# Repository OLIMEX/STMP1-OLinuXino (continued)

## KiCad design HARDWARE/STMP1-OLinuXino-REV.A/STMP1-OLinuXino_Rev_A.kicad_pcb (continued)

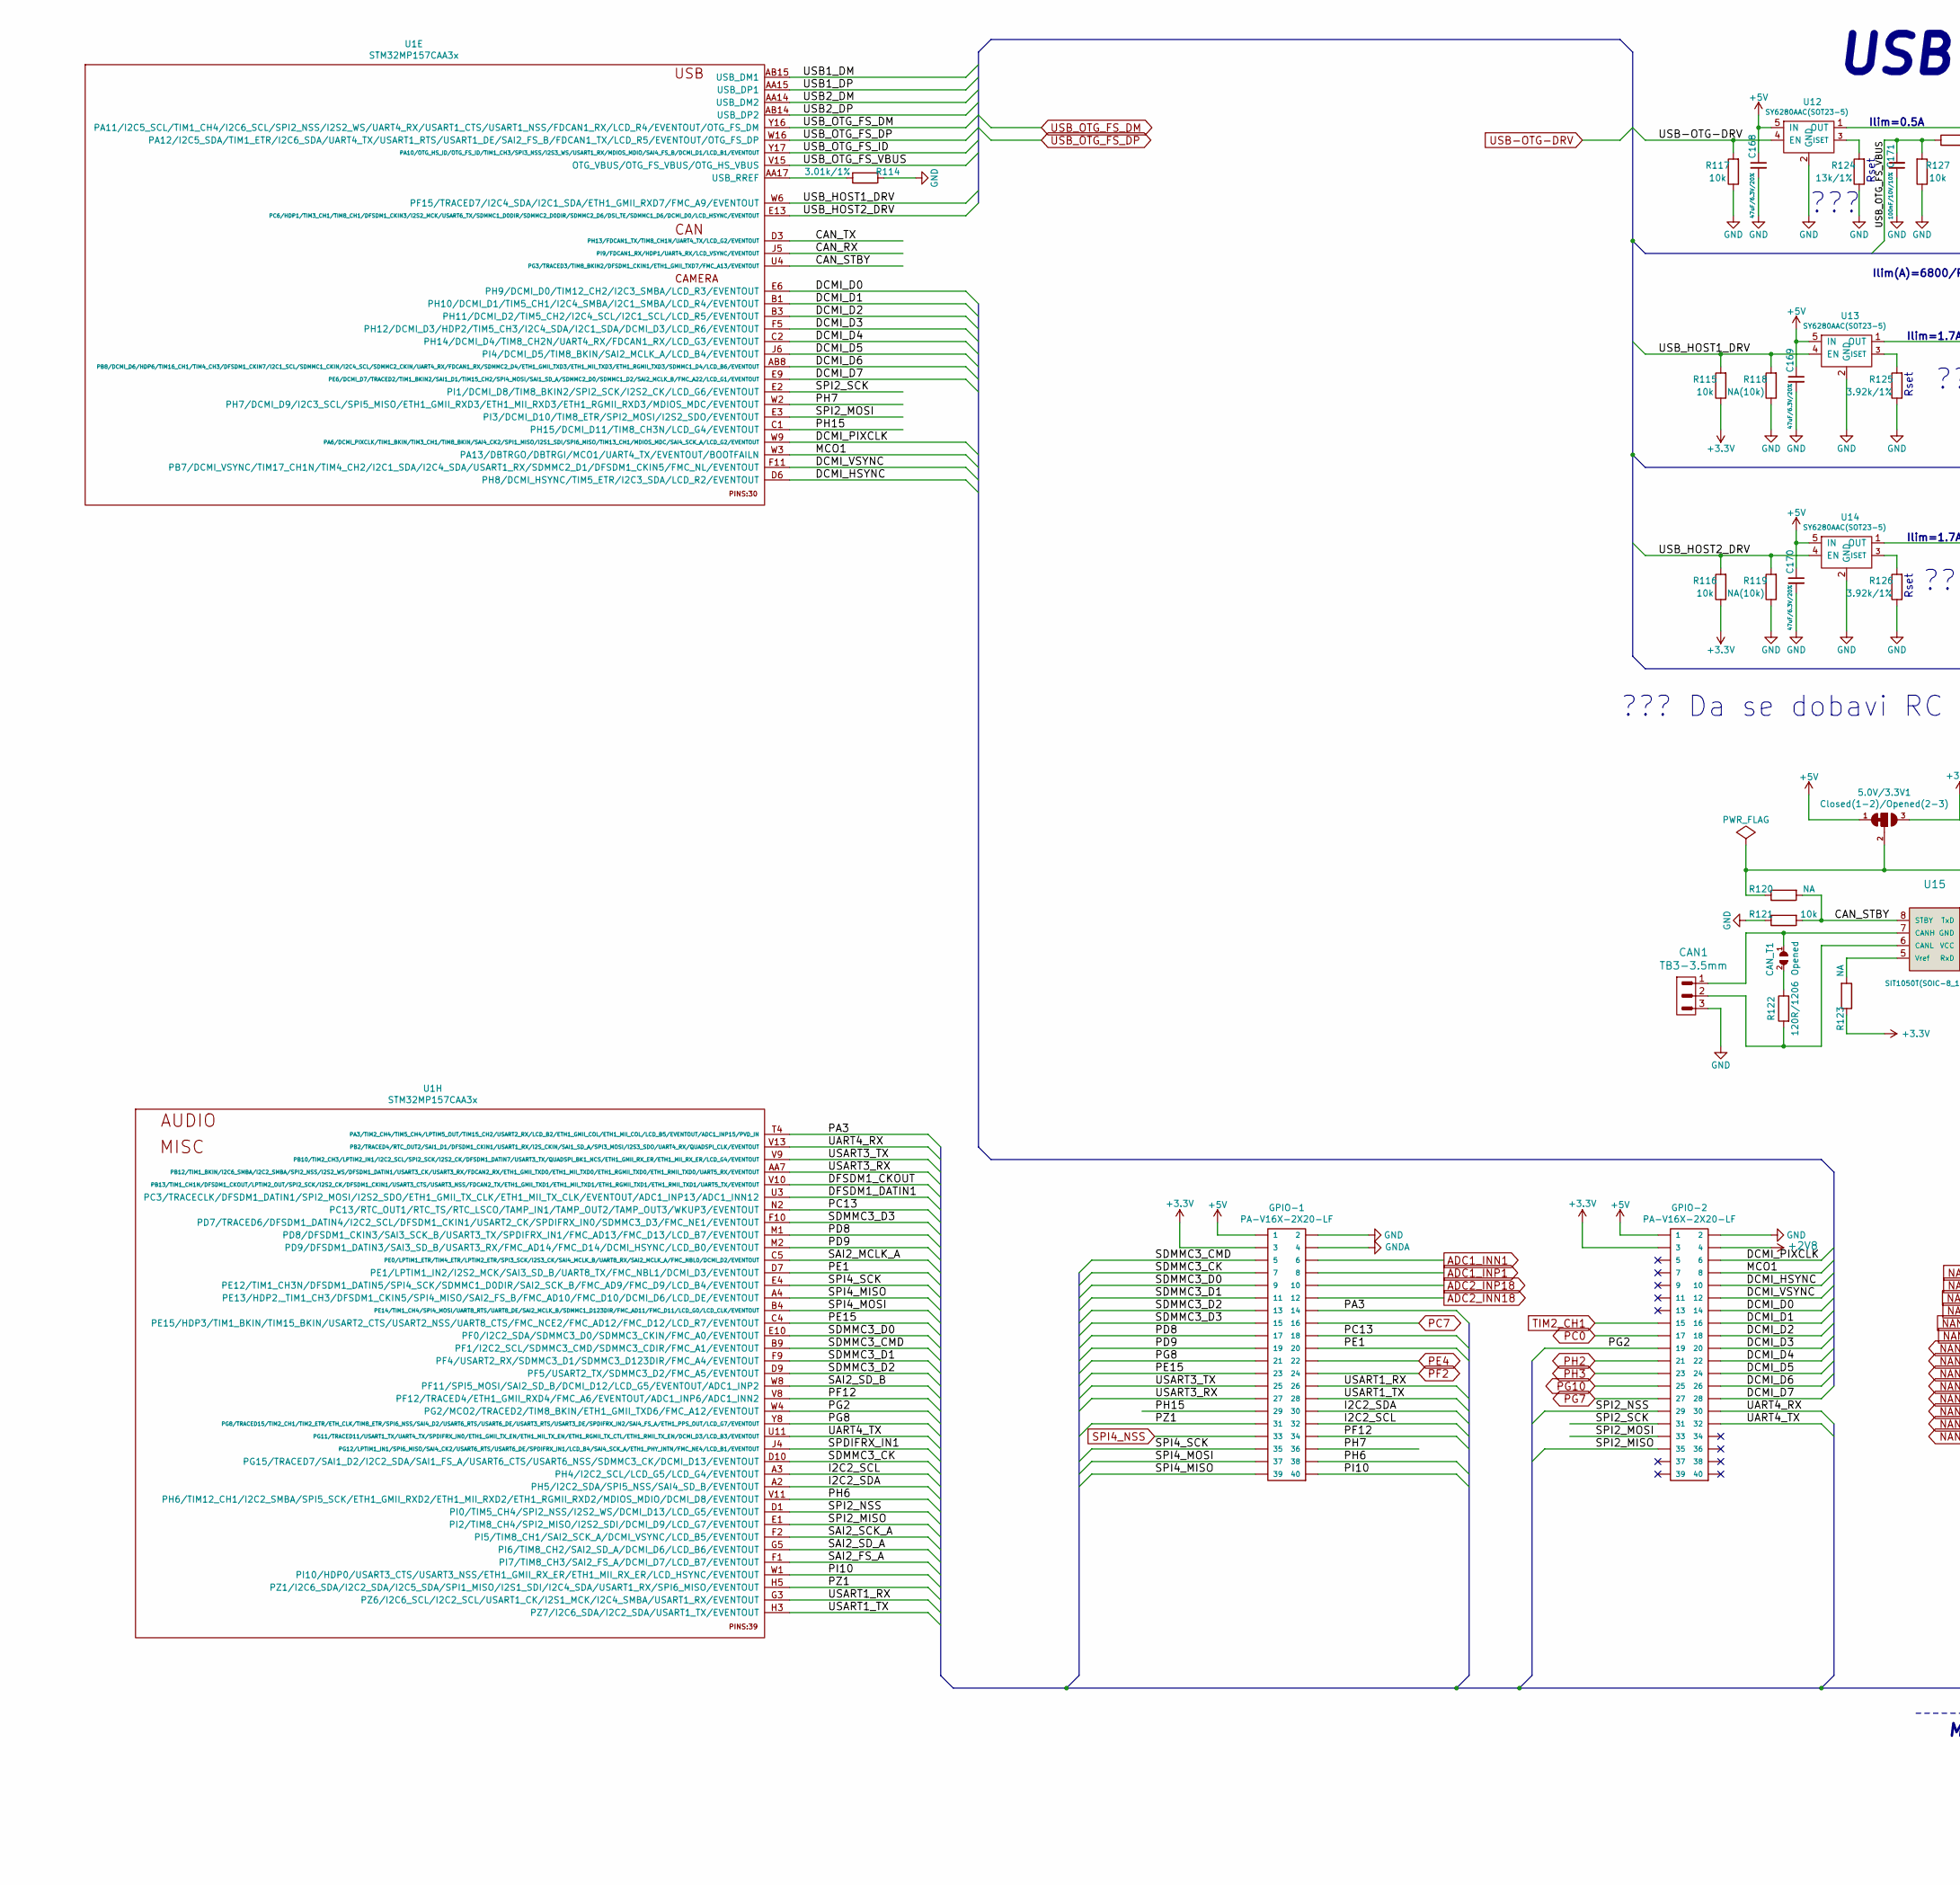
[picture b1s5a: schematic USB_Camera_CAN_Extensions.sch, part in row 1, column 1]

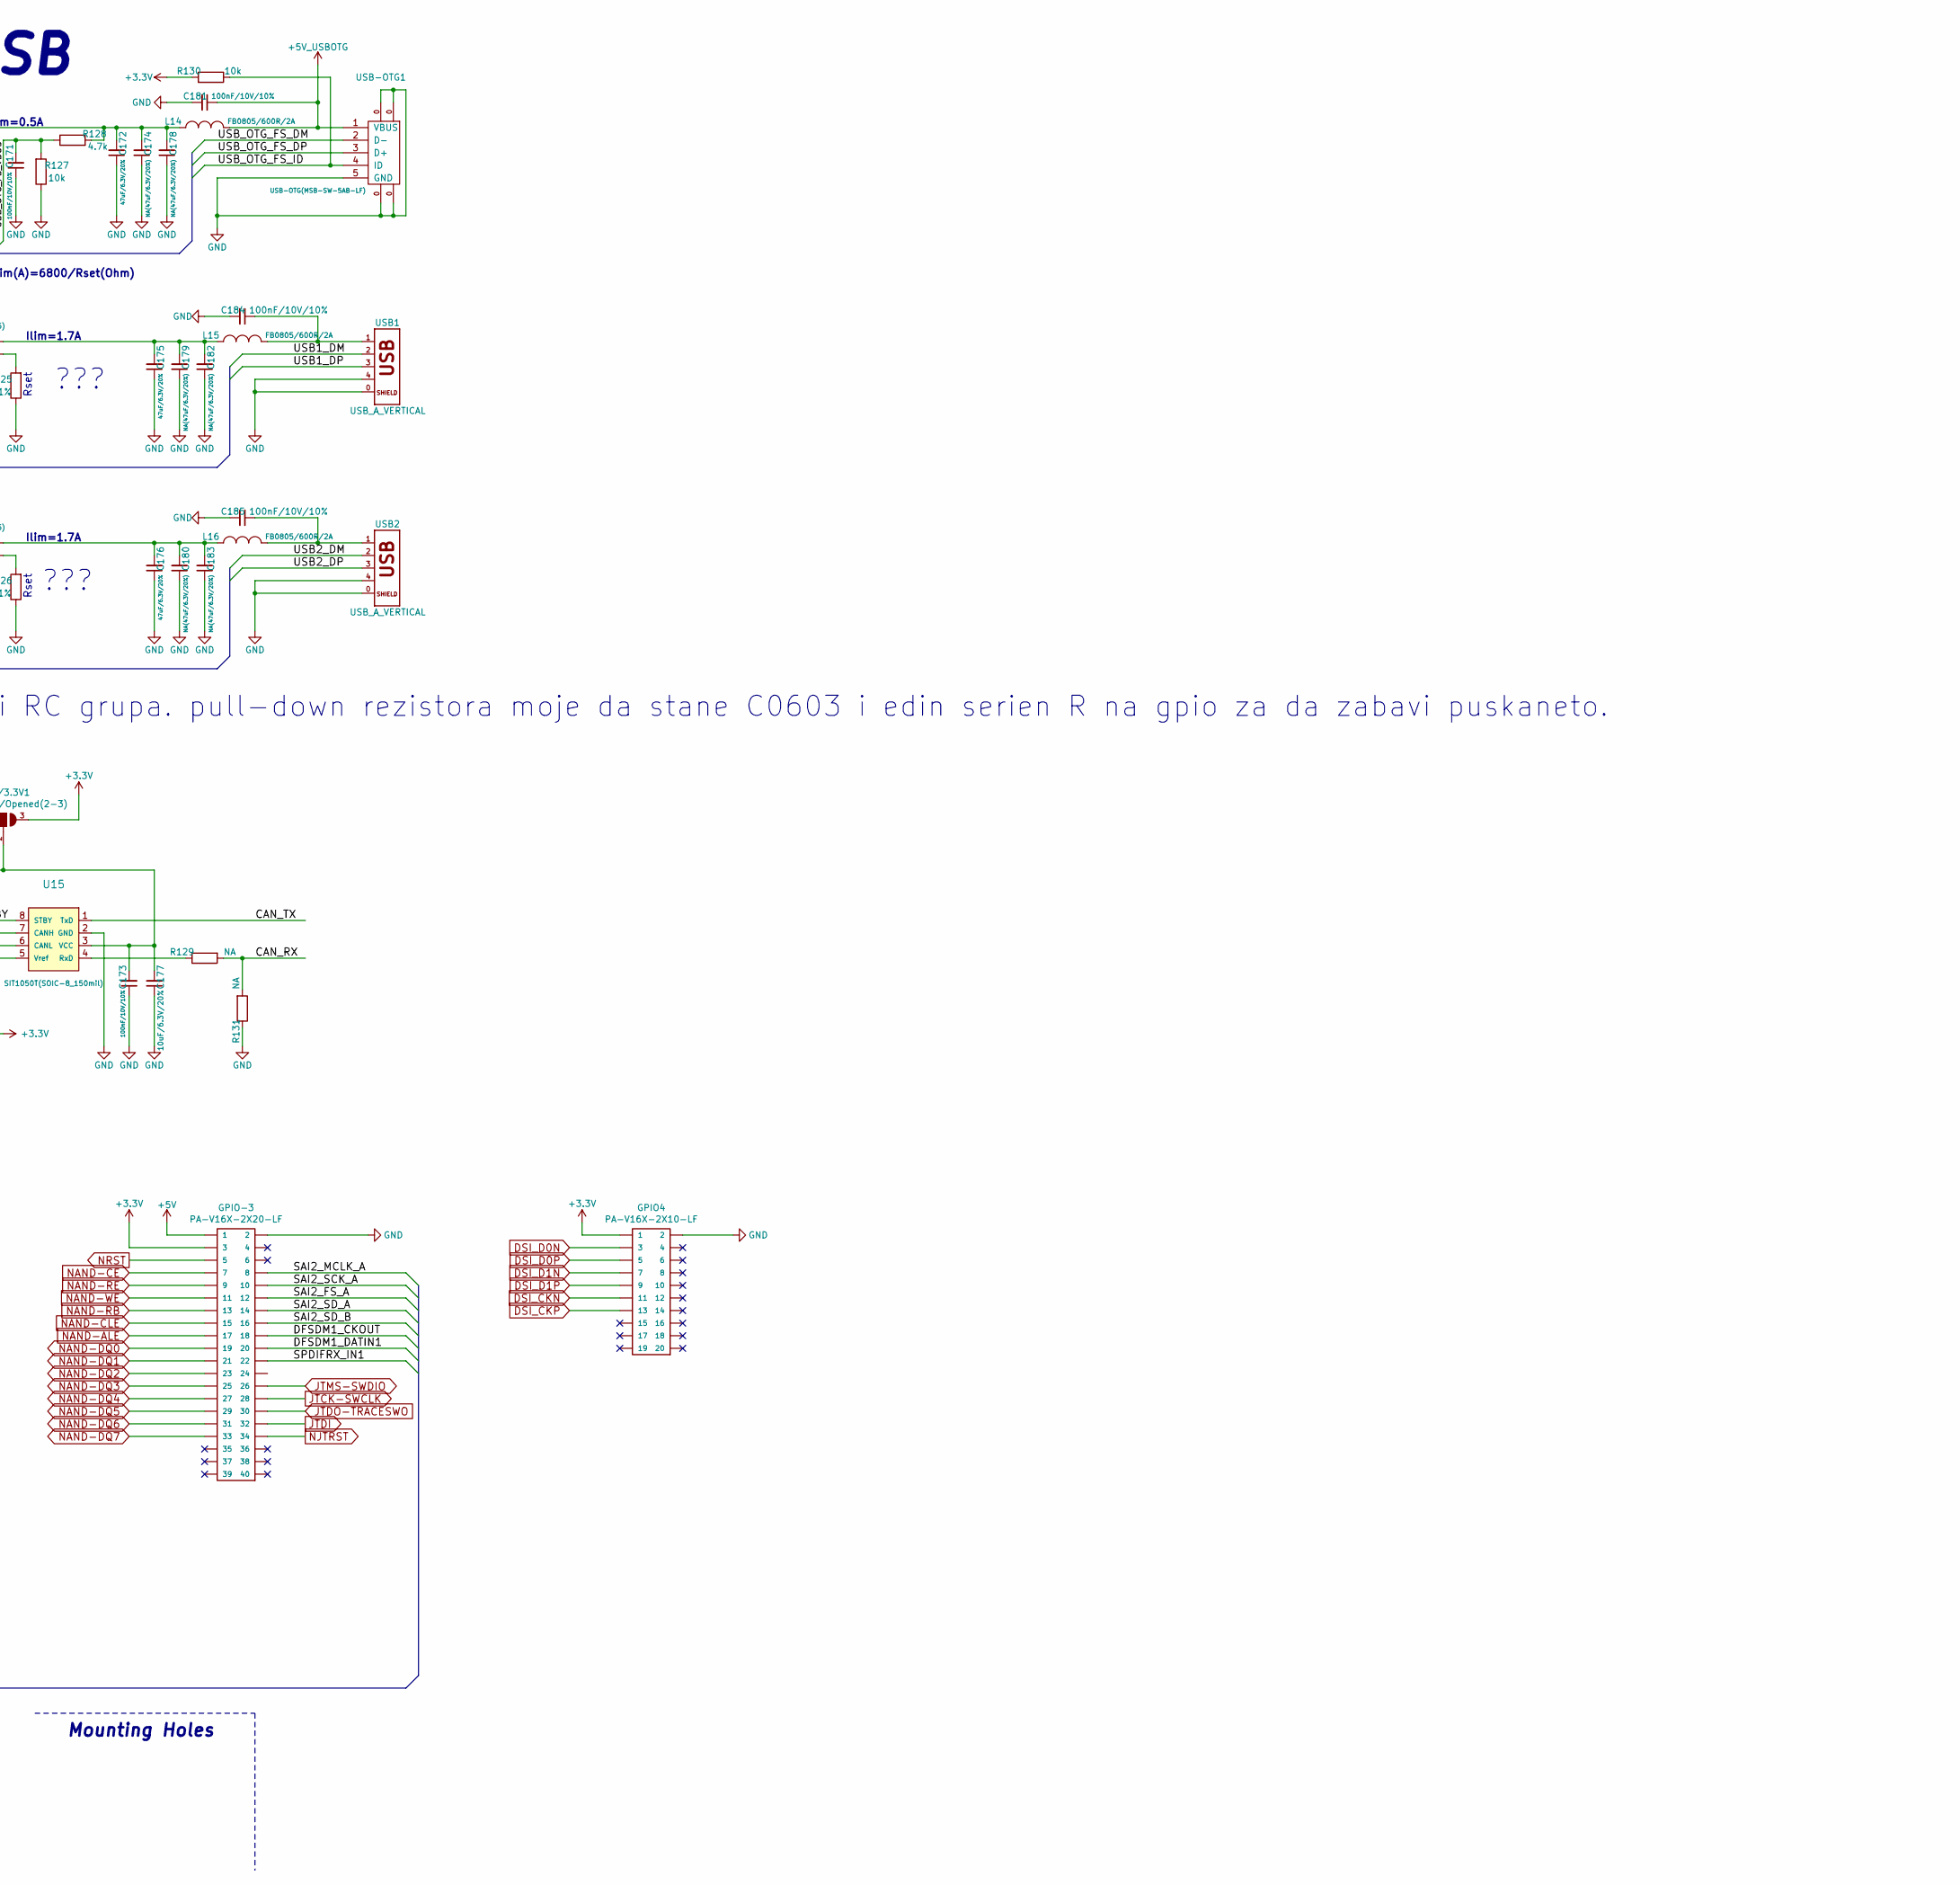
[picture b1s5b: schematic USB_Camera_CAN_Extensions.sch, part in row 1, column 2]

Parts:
5.0V/3.3V1: Closed(1-2)/Opened(2-3); SJ_2_SMALL_12_TIED
C168, C169, C170, C172, C175, C176: 47uF/6.3V/20%; C_0805_5MIL_DWS
C171, C173, C181, C184, C185: 100nF/10V/10%; C_0402_5MIL_DWS
C174, C178, C179, C180, C182, C183: NA(47uF/6.3V/20%); C_0805_5MIL_DWS
C177: 10uF/6.3V/20%; C_0603_5MIL_DWS
CAN1: TB3-3.5mm
CAN_T1: Opened; SJ_1_SMALLER
GPIO4: PA-V16X-2X10-LF; GPH127SMT-02X10(PA-V16X-2X10-LF)
GPIO-1, GPIO-2, GPIO-3: PA-V16X-2X20-LF; GPH127SMT-02X20(PA-V16X-2X20-LF)
L14, L15, L16: FB0805/600R/2A; L_0805_5MIL_DWS
R114: 3.01k/1%; R_0402_5MIL_DWS
R115, R116, R117, R121, R127, R130: 10k; R_0402_5MIL_DWS
R118, R119: NA(10k); R_0402_5MIL_DWS
R120, R123, R129, R131: NA; R_0402_5MIL_DWS
R122: 120R/1206; R_1206_5MIL_DWS
R124: 13k/1%; R_0402_5MIL_DWS
R125, R126: 3.92k/1%; R_0402_5MIL_DWS
R128: 4.7k; R_0402_5MIL_DWS
U1: STM32MP157CAA3x; LFBGA-448(Pitch-0.8mm_Pad-0.4mm_18x18x1.27mm)
U12, U13, U14: SY6280AAC(SOT23-5); SOT-23-5
U15: SIT1050T(SOIC-8_150mil); SOIC-8_150mil
USB1, USB2: USB_A_VERTICAL; USB_A_VERTICAL_PTH
USB-OTG1: USB-OTG(MSB-SW-5AB-LF); USB_MINI_9PIN

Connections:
+2V8: GPIO-2.4; also elsewhere on the board
+3V3: 5.0V/3.3V1.3, GPIO4.1, GPIO-1.3, GPIO-2.3, GPIO-3.3, R115.1, R116.1, R123.1, R130.2; also elsewhere on the board
+5V: 5.0V/3.3V1.1, C168.1, C169.1, C170.1, GPIO-1.1, GPIO-2.1, GPIO-3.1, U12.5 (IN), U13.5 (IN), U14.5 (IN); also elsewhere on the board
+5V_USBOTG: C181.1, L14.2, USB-OTG1.1 (VBUS); also elsewhere on the board
/USB_Camera_CAN_Extensions/CAN_RX: R129.2, R131.2, U1.J5 (PI9/FDCAN1_RX/HDP1/UART4_RX/LCD_VSYNC/E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)
/USB_Camera_CAN_Extensions/CAN_STBY: R120.2, R121.2, U1.U4 (PG3/TRACED3/TIM8_BKIN2/DFSDM1_CKIN1/ETH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), U15.8 (STBY)
/USB_Camera_CAN_Extensions/CAN_TX: U1.D3 (PH13/FDCAN1_TX/TIM8_CH1N/UART4_TX/LCD_G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), U15.1 (TxD)
/USB_Camera_CAN_Extensions/DCMI_D0: GPIO-2.14, U1.E6 (PH9/DCMI_D0/TIM12_CH2/I2C3_SMBA/LCD_R3/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)
/USB_Camera_CAN_Extensions/DCMI_D1: GPIO-2.16, U1.B1 (PH10/DCMI_D1/TIM5_CH1/I2C4_SMBA/I2C1_SM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)
/USB_Camera_CAN_Extensions/DCMI_D2: GPIO-2.18, U1.B3 (PH11/DCMI_D2/TIM5_CH2/I2C4_SCL/I2C1_SCL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)
/USB_Camera_CAN_Extensions/DCMI_D3: GPIO-2.20, U1.F5 (PH12/DCMI_D3/HDP2/TIM5_CH3/I2C4_SDA/I2C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)
/USB_Camera_CAN_Extensions/DCMI_D4: GPIO-2.22, U1.C2 (PH14/DCMI_D4/TIM8_CH2N/UART4_RX/FDCAN1_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)
/USB_Camera_CAN_Extensions/DCMI_D5: GPIO-2.24, U1.J6 (PI4/DCMI_D5/TIM8_BKIN/SAI2_MCLK_A/LCD_B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)
/USB_Camera_CAN_Extensions/DCMI_D6: GPIO-2.26, U1.AB8 (PB8/DCMI_D6/HDP6/TIM16_CH1/TIM4_CH3/DFS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)
/USB_Camera_CAN_Extensions/DCMI_D7: GPIO-2.28, U1.E9 (PE6/DCMI_D7/TRACED2/TIM1_BKIN2/SAI1_D1/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)
/USB_Camera_CAN_Extensions/DCMI_HSYNC: GPIO-2.10, U1.D6 (PH8/DCMI_HSYNC/TIM5_ETR/I2C3_SDA/LCD_R2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)
/USB_Camera_CAN_Extensions/DCMI_PIXCLK: GPIO-2.6, U1.W9 (PA6/DCMI_PIXCLK/TIM1_BKIN/TIM3_CH1/TIM8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)
/USB_Camera_CAN_Extensions/DCMI_VSYNC: GPIO-2.12, U1.F11 (PB7/DCMI_VSYNC/TIM17_CH1N/TIM4_CH2/I2C1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)
/USB_Camera_CAN_Extensions/DFSDM1_CKOUT: GPIO-3.18, U1.V10 (PB13/TIM1_CH1N/DFSDM1_CKOUT/LPTIM2_OUT/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)
/USB_Camera_CAN_Extensions/DFSDM1_DATIN1: GPIO-3.20, U1.U3 (PC3/TRACECLK/DFSDM1_DATIN1/SPI2_MOSI/I2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)
/USB_Camera_CAN_Extensions/I2C2_SCL: GPIO-1.32, U1.A3 (PH4/I2C2_SCL/LCD_G5/LCD_G4/EVENTOUT)
/USB_Camera_CAN_Extensions/I2C2_SDA: GPIO-1.30, U1.A2 (PH5/I2C2_SDA/SPI5_NSS/SAI4_SD_B/EVENTOUT)
/USB_Camera_CAN_Extensions/MCO1: GPIO-2.8, U1.W3 (PA13/DBTRGO/DBTRGI/MCO1/UART4_TX/EVENTO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)
/USB_Camera_CAN_Extensions/PA3: GPIO-1.14, U1.T4 (PA3/TIM2_CH4/TIM5_CH4/LPTIM5_OUT/TIM15_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)
/USB_Camera_CAN_Extensions/PC13: GPIO-1.18, U1.N2 (PC13/RTC_OUT1/RTC_TS/RTC_LSCO/TAMP_IN1/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)
/USB_Camera_CAN_Extensions/PD8: GPIO-1.17, U1.M1 (PD8/DFSDM1_CKIN3/SAI3_SCK_B/USART3_TX/S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)
/USB_Camera_CAN_Extensions/PD9: GPIO-1.19, U1.M2 (PD9/DFSDM1_DATIN3/SAI3_SD_B/USART3_RX/F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)
/USB_Camera_CAN_Extensions/PE1: GPIO-1.20, U1.D7 (PE1/LPTIM1_IN2/I2S2_MCK/SAI3_SD_B/UART8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)
/USB_Camera_CAN_Extensions/PE15: GPIO-1.23, U1.C4 (PE15/HDP3/TIM1_BKIN/TIM15_BKIN/USART2_C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)
/USB_Camera_CAN_Extensions/PF12: GPIO-1.34, U1.V8 (PF12/TRACED4/ETH1_GMII_RXD4/FMC_A6/EVEN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)
/USB_Camera_CAN_Extensions/PG2: GPIO-2.19, U1.W4 (PG2/MCO2/TRACED2/TIM8_BKIN/ETH1_GMII_TX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)
/USB_Camera_CAN_Extensions/PG8: GPIO-1.21, U1.Y8 (PG8/TRACED15/TIM2_CH1/TIM2_ETR/ETH_CLK/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)
/USB_Camera_CAN_Extensions/PH6: GPIO-1.38, U1.V11 (PH6/TIM12_CH1/I2C2_SMBA/SPI5_SCK/ETH1_G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)
/USB_Camera_CAN_Extensions/PH7: GPIO-1.36, U1.W2 (PH7/DCMI_D9/I2C3_SCL/SPI5_MISO/ETH1_GMI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)
/USB_Camera_CAN_Extensions/PH15: GPIO-1.29, U1.C1 (PH15/DCMI_D11/TIM8_CH3N/LCD_G4/EVENTOUT)
/USB_Camera_CAN_Extensions/PI10: GPIO-1.40, U1.W1 (PI10/HDP0/USART3_CTS/USART3_NSS/ETH1_GM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)
/USB_Camera_CAN_Extensions/PZ1: GPIO-1.31, U1.H5 (PZ1/I2C6_SDA/I2C2_SDA/I2C5_SDA/SPI1_MIS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)
/USB_Camera_CAN_Extensions/SAI2_FS_A: GPIO-3.12, U1.F1 (PI7/TIM8_CH3/SAI2_FS_A/DCMI_D7/LCD_B7/E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)
/USB_Camera_CAN_Extensions/SAI2_MCLK_A: GPIO-3.8, U1.C5 (PE0/LPTIM1_ETR/TIM4_ETR/LPTIM2_ETR/SPI3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)
/USB_Camera_CAN_Extensions/SAI2_SCK_A: GPIO-3.10, U1.F2 (PI5/TIM8_CH1/SAI2_SCK_A/DCMI_VSYNC/LCD_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)
/USB_Camera_CAN_Extensions/SAI2_SD_A: GPIO-3.14, U1.G5 (PI6/TIM8_CH2/SAI2_SD_A/DCMI_D6/LCD_B6/E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)
/USB_Camera_CAN_Extensions/SAI2_SD_B: GPIO-3.16, U1.W8 (PF11/SPI5_MOSI/SAI2_SD_B/DCMI_D12/LCD_G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)
/USB_Camera_CAN_Extensions/SDMMC3_CK: GPIO-1.7, U1.D10 (PG15/TRACED7/SAI1_D2/I2C2_SDA/SAI1_FS_A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)
/USB_Camera_CAN_Extensions/SDMMC3_CMD: GPIO-1.5, U1.B9 (PF1/I2C2_SCL/SDMMC3_CMD/SDMMC3_CDIR/FMC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)
/USB_Camera_CAN_Extensions/SDMMC3_D0: GPIO-1.9, U1.E10 (PF0/I2C2_SDA/SDMMC3_D0/SDMMC3_CKIN/FMC_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)
/USB_Camera_CAN_Extensions/SDMMC3_D1: GPIO-1.11, U1.F9 (PF4/USART2_RX/SDMMC3_D1/SDMMC3_D123DIR/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)
/USB_Camera_CAN_Extensions/SDMMC3_D2: GPIO-1.13, U1.D9 (PF5/USART2_TX/SDMMC3_D2/FMC_A5/EVENTOUT)
/USB_Camera_CAN_Extensions/SDMMC3_D3: GPIO-1.15, U1.F10 (PD7/TRACED6/DFSDM1_DATIN4/I2C2_SCL/DFSD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)
/USB_Camera_CAN_Extensions/SPDIFRX_IN1: GPIO-3.22, U1.J4 (PG12/LPTIM1_IN1/SPI6_MISO/SAI4_CK2/USAR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)
/USB_Camera_CAN_Extensions/SPI2_MISO: GPIO-2.35, U1.E1 (PI2/TIM8_CH4/SPI2_MISO/I2S2_SDI/DCMI_D9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)
/USB_Camera_CAN_Extensions/SPI2_MOSI: GPIO-2.33, U1.E3 (PI3/DCMI_D10/TIM8_ETR/SPI2_MOSI/I2S2_SD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)
/USB_Camera_CAN_Extensions/SPI2_NSS: GPIO-2.29, U1.D1 (PI0/TIM5_CH4/SPI2_NSS/I2S2_WS/DCMI_D13/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)
/USB_Camera_CAN_Extensions/SPI2_SCK: GPIO-2.31, U1.E2 (PI1/DCMI_D8/TIM8_BKIN2/SPI2_SCK/I2S2_CK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)
/USB_Camera_CAN_Extensions/SPI4_MISO: GPIO-1.39, U1.A4 (PE13/HDP2,_TIM1_CH3/DFSDM1_CKIN5/SPI4_M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)
/USB_Camera_CAN_Extensions/SPI4_MOSI: GPIO-1.37, U1.B4 (PE14/TIM1_CH4/SPI4_MOSI/UART8_RTS/UART8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)
/USB_Camera_CAN_Extensions/SPI4_SCK: GPIO-1.35, U1.E4 (PE12/TIM1_CH3N/DFSDM1_DATIN5/SPI4_SCK/S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)
/USB_Camera_CAN_Extensions/UART4_RX: GPIO-2.30, U1.V13 (PB2/TRACED4/RTC_OUT2/SAI1_D1/DFSDM1_CKI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)
/USB_Camera_CAN_Extensions/UART4_TX: GPIO-2.32, U1.U11 (PG11/TRACED11/USART1_TX/UART4_TX/SPDIFR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)
/USB_Camera_CAN_Extensions/USART1_RX: GPIO-1.26, U1.G3 (PZ6/I2C6_SCL/I2C2_SCL/USART1_CK/I2S1_MC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)
/USB_Camera_CAN_Extensions/USART1_TX: GPIO-1.28, U1.H3 (PZ7/I2C6_SDA/I2C2_SDA/USART1_TX/EVENTOUT)
/USB_Camera_CAN_Extensions/USART3_RX: GPIO-1.27, U1.AA7 (PB12/TIM1_BKIN/I2C6_SMBA/I2C2_SMBA/SPI2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)
/USB_Camera_CAN_Extensions/USART3_TX: GPIO-1.25, U1.V9 (PB10/TIM2_CH3/LPTIM2_IN1/I2C2_SCL/SPI2_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)
/USB_Camera_CAN_Extensions/USB1_DM: U1.AB15 (USB_DM1), USB1.2
/USB_Camera_CAN_Extensions/USB1_DP: U1.AA15 (USB_DP1), USB1.3
/USB_Camera_CAN_Extensions/USB2_DM: U1.AA14 (USB_DM2), USB2.2
/USB_Camera_CAN_Extensions/USB2_DP: U1.AB14 (USB_DP2), USB2.3
/USB_Camera_CAN_Extensions/USB_HOST1_DRV: R115.2, R118.2, U1.W6 (PF15/TRACED7/I2C4_SDA/I2C1_SDA/ETH1_GMI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), U13.4 (EN)
/USB_Camera_CAN_Extensions/USB_HOST2_DRV: R116.2, R119.2, U1.E13 (PC6/HDP1/TIM3_CH1/TIM8_CH1/DFSDM1_CKIN3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), U14.4 (EN)
/USB_Camera_CAN_Extensions/USB_OTG_FS_ID: R130.1, U1.Y17 (PA10/OTG_HS_ID/OTG_FS_ID/TIM1_CH3/SPI3_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), USB-OTG1.4 (ID)
/USB_Camera_CAN_Extensions/USB_OTG_FS_VBUS: C171.2, R127.2, R128.1, U1.V15 (OTG_VBUS/OTG_FS_VBUS/OTG_HS_VBUS)
ADC1_INN1: GPIO-1.6; also elsewhere on the board
ADC1_INP1: GPIO-1.8; also elsewhere on the board
ADC2_INN18: GPIO-1.12; also elsewhere on the board
ADC2_INP18: GPIO-1.10; also elsewhere on the board
DSI_CKN: GPIO4.11; also elsewhere on the board
DSI_CKP: GPIO4.13; also elsewhere on the board
DSI_D0N: GPIO4.3; also elsewhere on the board
DSI_D0P: GPIO4.5; also elsewhere on the board
DSI_D1N: GPIO4.7; also elsewhere on the board
DSI_D1P: GPIO4.9; also elsewhere on the board
GND: C168.2, C169.2, C170.2, C171.1, C172.1, C173.1, C174.1, C175.1, C176.1, C177.1, C178.1, C179.1, C180.1, C181.2, C182.1, C183.1, C184.2, C185.2, CAN1.3, GPIO4.2, GPIO-1.2, GPIO-2.2, GPIO-3.2, R114.1, R117.1, R118.1, R119.1, R121.1, R124.1, R125.1, R126.1, R127.1, R131.1, U12.2 (GND), U13.2 (GND), U14.2 (GND), U15.2 (GND), USB1.0 (5), USB1.4, USB2.0 (5), USB2.4, USB-OTG1.0, USB-OTG1.5 (GND); also elsewhere on the board
GNDA: GPIO-1.4; also elsewhere on the board
JTCK-SWCLK: GPIO-3.28; also elsewhere on the board
JTDI: GPIO-3.32; also elsewhere on the board
JTDO-TRACESWO: GPIO-3.30; also elsewhere on the board
JTMS-SWDIO: GPIO-3.26; also elsewhere on the board
NAND-ALE: GPIO-3.17; also elsewhere on the board
NAND-CE: GPIO-3.7; also elsewhere on the board
NAND-CLE: GPIO-3.15; also elsewhere on the board
NAND-DQ0: GPIO-3.19; also elsewhere on the board
NAND-DQ1: GPIO-3.21; also elsewhere on the board
NAND-DQ2: GPIO-3.23; also elsewhere on the board
NAND-DQ3: GPIO-3.25; also elsewhere on the board
NAND-DQ4: GPIO-3.27; also elsewhere on the board
NAND-DQ5: GPIO-3.29; also elsewhere on the board
NAND-DQ6: GPIO-3.31; also elsewhere on the board
NAND-DQ7: GPIO-3.33; also elsewhere on the board
NAND-RB: GPIO-3.13; also elsewhere on the board
NAND-RE: GPIO-3.9; also elsewhere on the board
NAND-WE: GPIO-3.11; also elsewhere on the board
NJTRST: GPIO-3.34; also elsewhere on the board
NRST: GPIO-3.5; also elsewhere on the board
unnamed: 5.0V/3.3V1.2, C173.2, C177.2, R120.1, U15.3 (VCC)
unnamed: C172.2, C174.2, C178.2, L14.1, R128.2, U12.1 (OUT)
unnamed: C175.2, C179.2, C182.2, L15.1, U13.1 (OUT)
unnamed: C176.2, C180.2, C183.2, L16.1, U14.1 (OUT)
unnamed: C184.1, L15.2, USB1.1
unnamed: C185.1, L16.2, USB2.1
unnamed: CAN1.1, CAN_T1.1, U15.7 (CANH)
unnamed: CAN1.2, R122.2, U15.6 (CANL)
unnamed: CAN_T1.2, R122.1
unnamed: R114.2, U1.AA17 (USB_RREF)
unnamed: R123.2, U15.5 (Vref)
unnamed: R124.2, U12.3 (ISET)
unnamed: R125.2, U13.3 (ISET)
unnamed: R126.2, U14.3 (ISET)
unnamed: R129.1, U15.4 (RxD)
PC0: GPIO-2.17; also elsewhere on the board
PC7: GPIO-1.16; also elsewhere on the board
PE4: GPIO-1.22; also elsewhere on the board
PF2: GPIO-1.24; also elsewhere on the board
PG7: GPIO-2.27; also elsewhere on the board
PG10: GPIO-2.25; also elsewhere on the board
PH2: GPIO-2.21; also elsewhere on the board
PH3: GPIO-2.23; also elsewhere on the board
SPI4_NSS: GPIO-1.33; also elsewhere on the board
TIM2_CH1: GPIO-2.15; also elsewhere on the board
USB-OTG-DRV: R117.2, U12.4 (EN); also elsewhere on the board
USB_OTG_FS_DM: U1.Y16 (PA11/I2C5_SCL/TIM1_CH4/I2C6_SCL/SPI2_NS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), USB-OTG1.2 (D-); also elsewhere on the board
USB_OTG_FS_DP: U1.W16 (PA12/I2C5_SDA/TIM1_ETR/I2C6_SDA/UART4_T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), USB-OTG1.3 (D+); also elsewhere on the board

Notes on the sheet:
USB
Ilim(A)=6800/Rset(Ohm)
Rset
Ilim=1.7A
Ilim=0.5A
???
??? Da se dobavi RC grupa. pull-down rezistora moje da stane C0603 i edin serien R na gpio za da zabavi puskaneto.
Mounting Holes

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
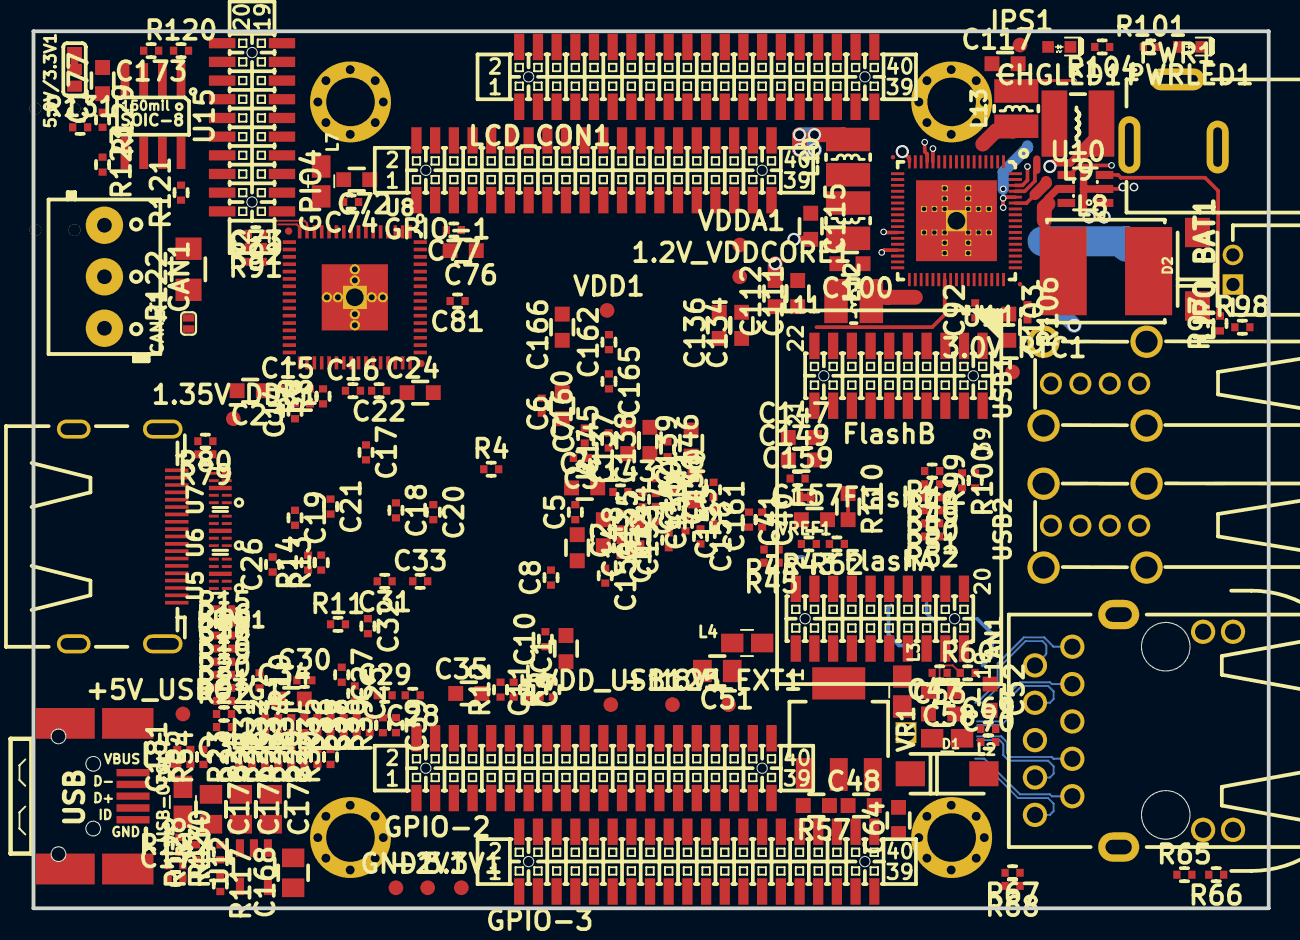
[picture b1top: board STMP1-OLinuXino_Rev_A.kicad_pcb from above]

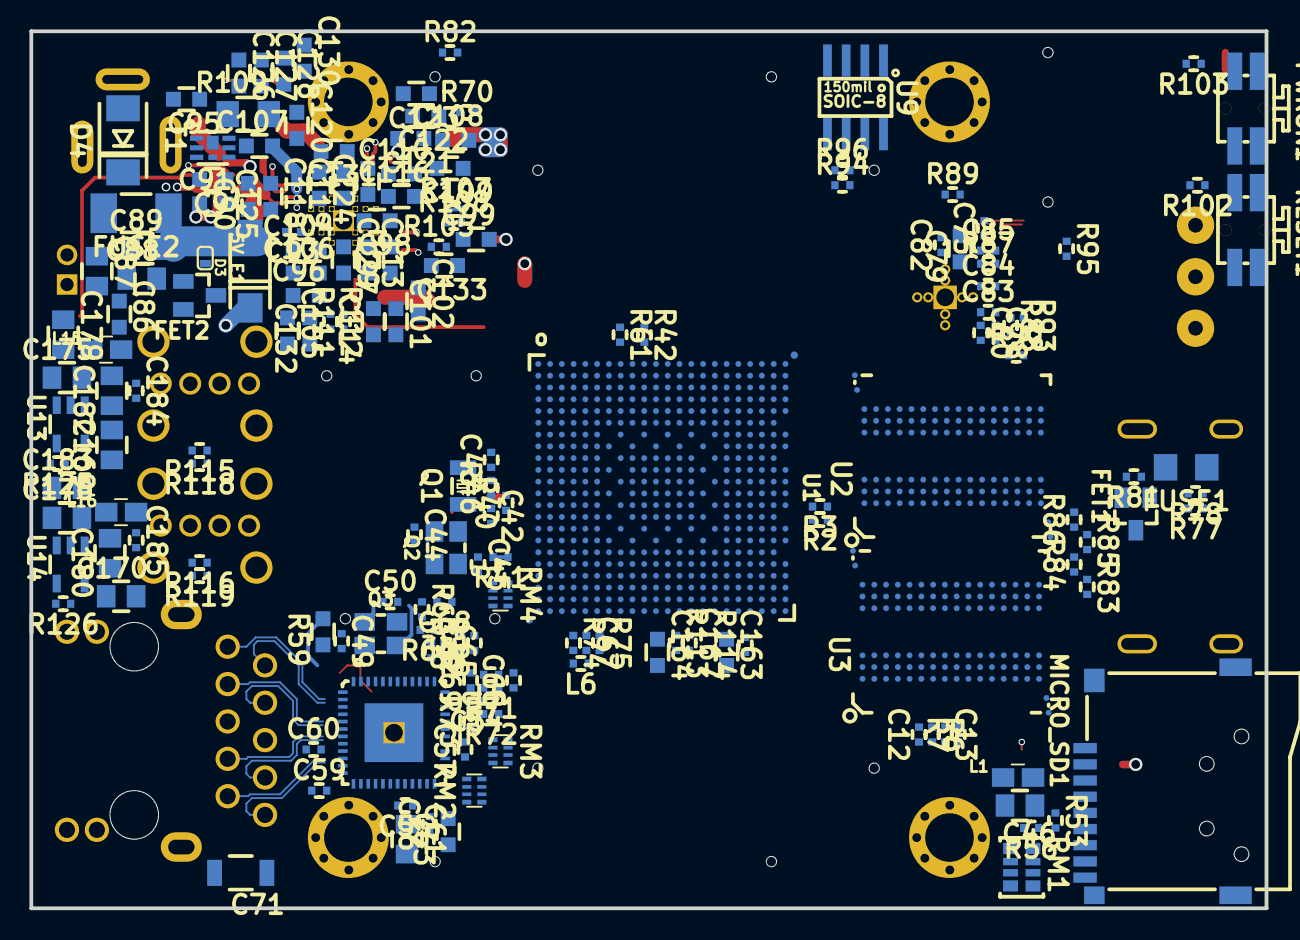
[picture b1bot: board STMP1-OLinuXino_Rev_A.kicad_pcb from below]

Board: 8 copper layers, 84.0 x 59.6 mm, 400 parts (170 on the bottom side), 420 nets.

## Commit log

2019-12-10 initial upload hardware files and 3d view
